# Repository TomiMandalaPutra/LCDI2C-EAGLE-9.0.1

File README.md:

# LCDI2C-EAGLE-9.0.1
This is file schematic, board, and gerber 274x

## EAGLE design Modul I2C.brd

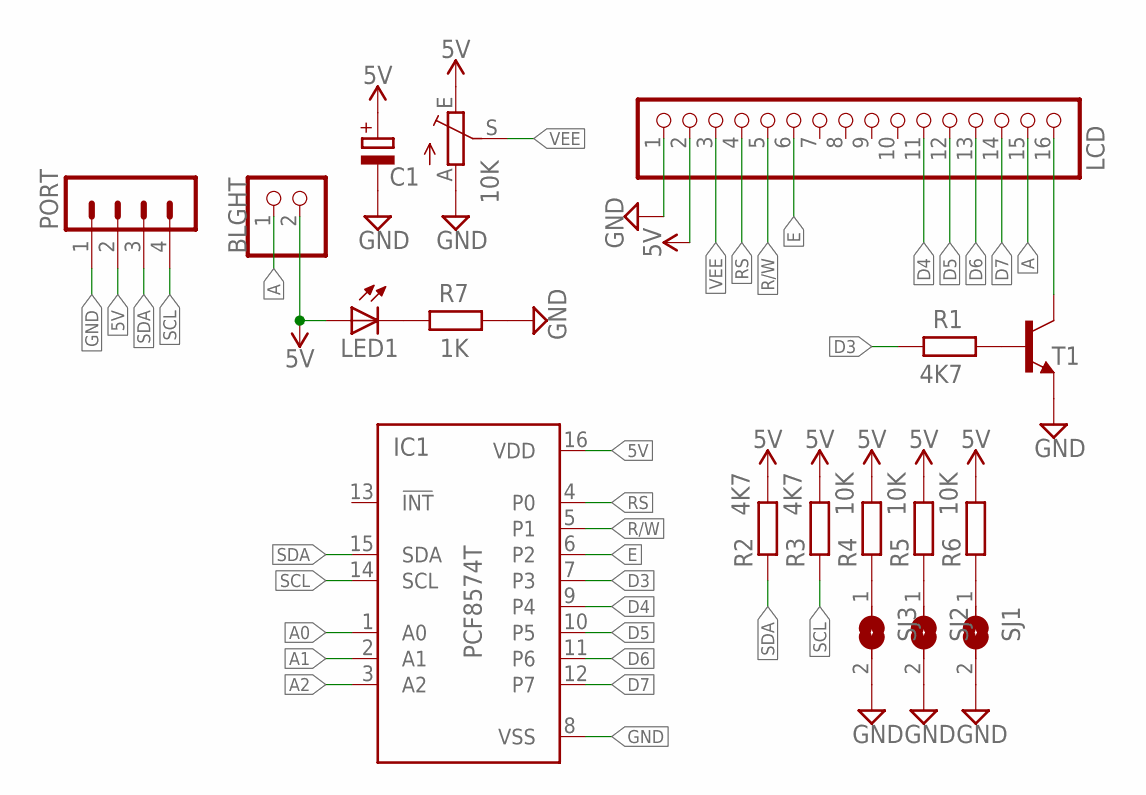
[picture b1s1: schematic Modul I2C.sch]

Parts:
10K: TRIM_EU-CT6; CT6
BLGHT: PINHD-1X2; 1X02
C1: CPOL-EUE2.5-5; E2,5-5
IC1: PCF8574T; SO16W
LCD: PINHD-1X16; 1X16
LED1: LED3MM
PORT: MA04-1
R1, R2, R3: 4K7; R0805
R4, R5, R6: 10K; R0805
R7: 1K; R0805
SJ1, SJ2, SJ3: SJ
T1: MMBT918LT1-NPN-SOT23-BEC; SOT23-BEC

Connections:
5V: 10K.E, BLGHT.2, C1.+, IC1.16 (VDD), LCD.2, LED1.A, PORT.2, R2.2, R3.2, R4.2, R5.2, R6.2
A: BLGHT.1, LCD.15
A0: IC1.1 (A0)
A1: IC1.2 (A1)
A2: IC1.3 (A2)
D3: IC1.7 (P3), R1.2
D4: IC1.9 (P4), LCD.11
D5: IC1.10 (P5), LCD.12
D6: IC1.11 (P6), LCD.13
D7: IC1.12 (P7), LCD.14
E: IC1.6 (P2), LCD.6
GND: 10K.A, C1.-, IC1.8 (VSS), LCD.1, PORT.1, R7.1, SJ1.2, SJ2.2, SJ3.2, T1.E
K: LCD.16, T1.C
unnamed: R1.1, T1.B
unnamed: R6.1, SJ1.1
unnamed: R5.1, SJ2.1
unnamed: R4.1, SJ3.1
unnamed: LED1.K (C), R7.2
R/W: IC1.5 (P1), LCD.5
RS: IC1.4 (P0), LCD.4
SCL: IC1.14 (SCL), PORT.4, R3.1
SDA: IC1.15 (SDA), PORT.3, R2.1
VEE: 10K.S, LCD.3

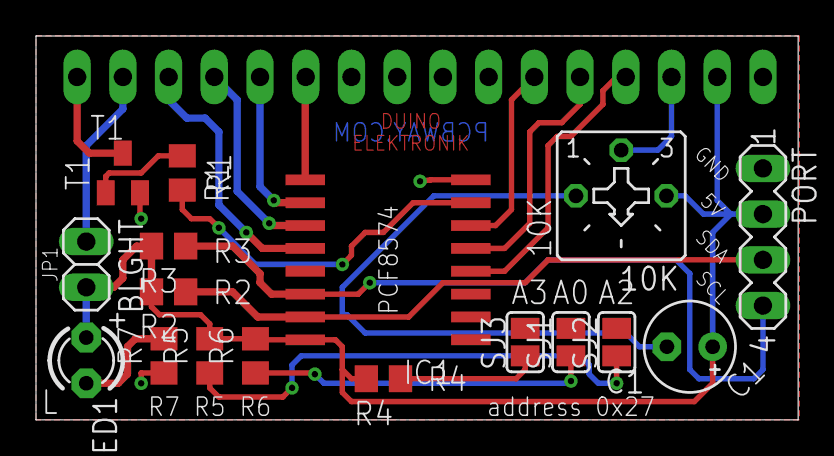
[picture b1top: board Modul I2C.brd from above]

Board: 2 copper layers, 42.3 x 21.3 mm, 18 parts (1 on the bottom side), 20 nets.

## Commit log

2019-08-09 Open Source
    Open source schematic, board, and gerb 274x EAGLE 9.0.1
    List component :
    1. Resistor 10K 0805
    2. Resistor 4k7 0805
    3. Resistor 1K 0805
    4. Transistor NPN SMD

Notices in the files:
parts and their libraries:
SparkFun-PowerSymbols: Licensing: Creative Commons ShareAlike 4.0 International - https://creativecommons.org/licenses/by-sa/4.0
